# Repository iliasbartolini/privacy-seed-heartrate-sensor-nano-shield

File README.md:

# Privacy Seed - Heart rate sensor nano shield

KiCAD shield shield for Arduino Nano to connect a [heart rate sensor board](https://github.com/iliasbartolini/privacy-seed-heartrate-sensor-board).
This component is part of the [Privacy Seed](https://privacy-seed.org/) project.

## Schema

## PCB

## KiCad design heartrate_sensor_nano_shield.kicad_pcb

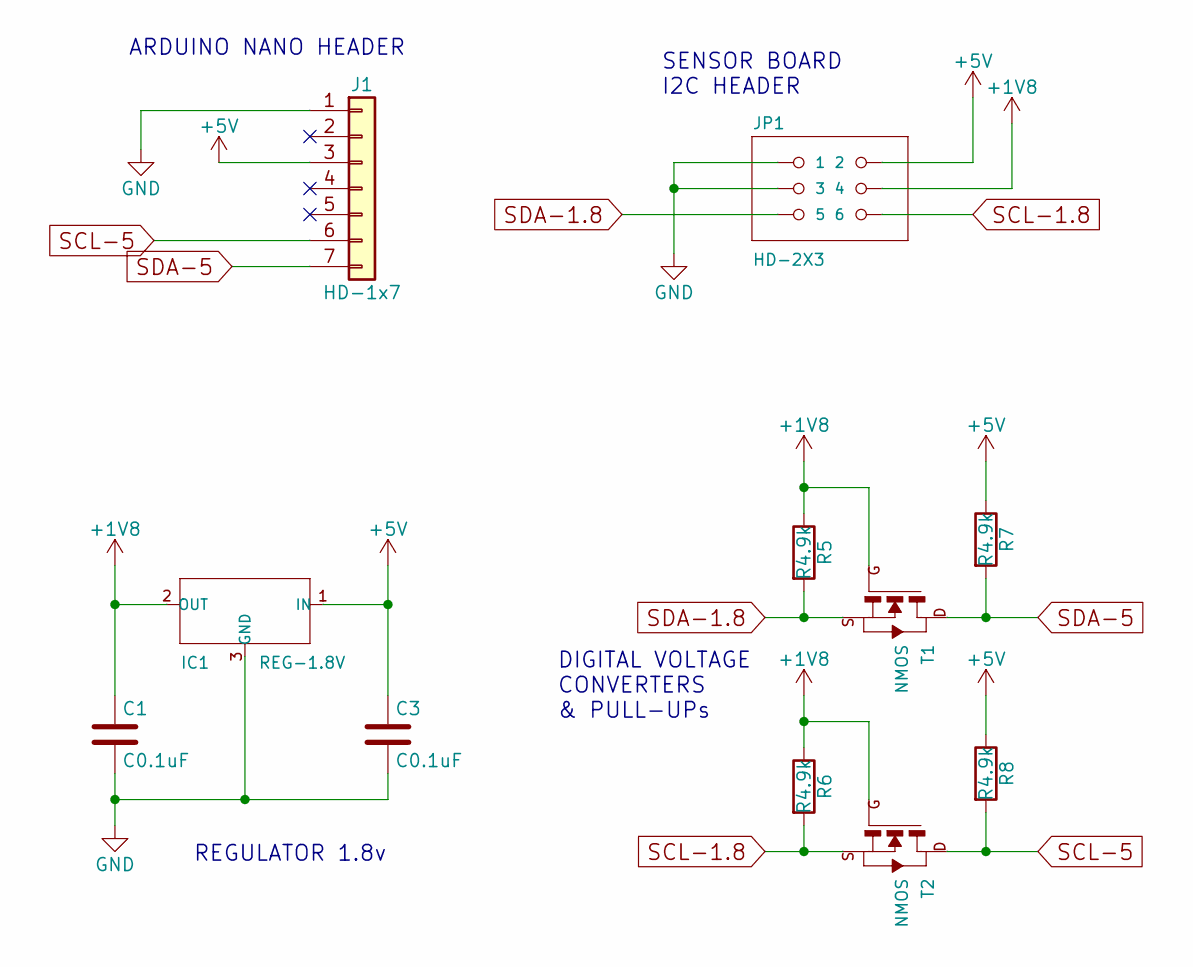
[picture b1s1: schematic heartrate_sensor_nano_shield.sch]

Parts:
C1, C3: C0.1uF; fab-C1206FAB
IC1: REG-1.8V; fab-SOT23
J1: HD-1x7; fab-1X07SMD-THROUGH
JP1: HD-2X3; fab-2X03SMD
R5, R6, R7, R8: R4.9k; fab-R1206FAB
T1, T2: NMOS; fab-SOT-23

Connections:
+1V8: C1.1, IC1.2 (OUT), JP1.4, R5.1, R6.1, T1.3 (G), T2.3 (G)
+5V: C3.1, IC1.1 (IN), J1.3, JP1.2, R7.1, R8.1
GND: C1.2, C3.2, IC1.3 (GND), J1.1, JP1.1, JP1.3
SCL-1.8: JP1.6, R6.2, T2.2 (S)
SCL-5: J1.6, R8.2, T2.1 (D)
SDA-1.8: JP1.5, R5.2, T1.2 (S)
SDA-5: J1.7, R7.2, T1.1 (D)

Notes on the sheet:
SENSOR BOARD I2C HEADER
ARDUINO NANO HEADER
DIGITAL VOLTAGE CONVERTERS & PULL-UPs
REGULATOR 1.8v

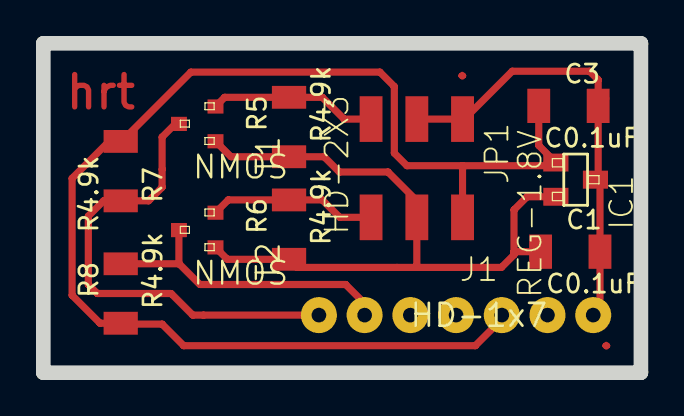
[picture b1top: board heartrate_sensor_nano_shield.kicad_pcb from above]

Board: 2 copper layers, 33.2 x 18.3 mm, 11 parts (0 on the bottom side), 7 nets.

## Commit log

2018-10-29 Added license and readme
2018-10-29 URL fix
2018-10-29 Fix images path
